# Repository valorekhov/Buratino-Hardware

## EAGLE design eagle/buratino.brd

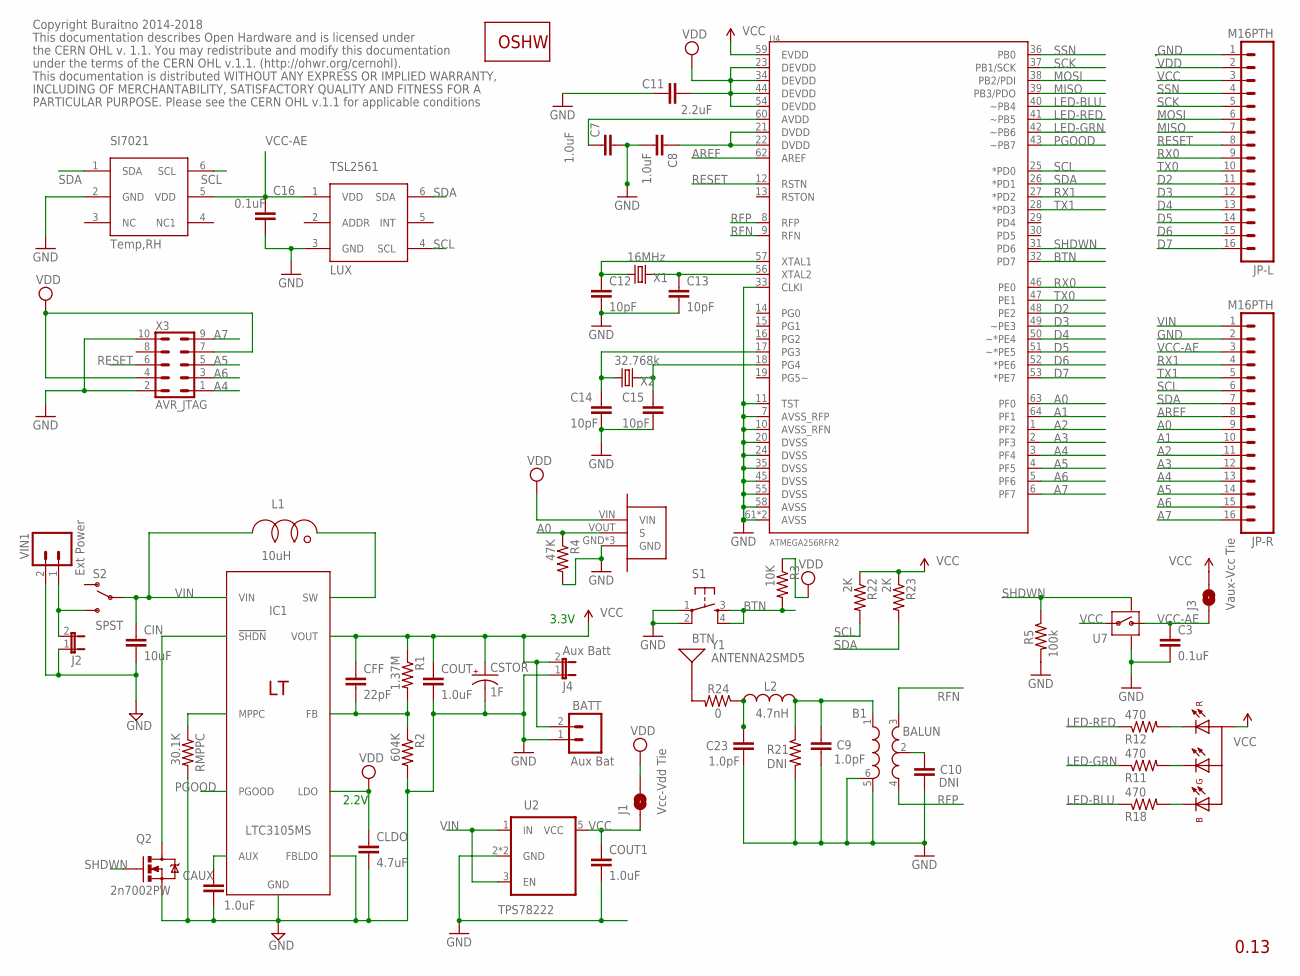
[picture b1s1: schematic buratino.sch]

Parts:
B1: BALUN
BATT: Aux Bat; JST-SFH
C3, C16: 0.1uF; 0603-CAP
C7, C8: 1.0uF; 0603-CAP
C9, C23: 1.0pF; 0402-CAP
C10: DNI; 0402-CAP
C11: 2.2uF; 0603-CAP
C12, C13, C14, C15: 10pF; 0402-CAP
CAUX: 1.0uF; 0603-CAP
CFF: 22pF; 0603-CAP
CIN: 10uF; 0805
CLDO: 4.7uF; 0603-CAP
COUT, COUT1: 1.0uF; 0603-CAP
CSTOR: 1F; SCAP1
IC1: LTC3105MS; MSOP12
J1: Vcc-Vdd Tie; SJ_2S-NO
J2: Ext Battery; 1X02
J3: Vaux-Vcc Tie; SJ_2S-NO
J4: Aux Batt; 1X02
JP-L: M16PTH; 1X16
JP-R: M16PTH; 1X16
L1: 10uH; NR2
L2: 4.7nH; 0402-CAP
PIR: IRS-B210ST01R1; PIRSMT
Q2: 2n7002PW; SOT323
R1: 1.37M; 0603-RES
R2: 604K; 0603-RES
R3: 10K; 0603-RES
R4: 47K; 0603-RES
R5: 100k; 0603-RES
R11, R12, R18: 470; 0603-RES
R21: DNI; 0402-RES
R22, R23: 2K; 0603-RES
R24: 0; 0402-RES
RMPPC: 30.1K; 0603-RES
S1: BTN; TACTILE-PTH
S2: SPST; SWITCH-SPDT-SMD
SI7021: Temp,RH; DFN6-3X3
TSL2561: LUX; DFN6-2X2
U2: TPS78222; SOT23-5
U4: ATMEGA256RFR2; QFN-64
U7: SWITCH; TDFN4
U8: LED-RGB; PLCC4
U$2: LOGO-OSHWSILKSCREEN; LOGO-OSHW-SS
VIN1: Ext Power; JST-SFH
X1: 16MHz; CRYSTAL-SMD-2.5X2-ABM10
X2: 32.768k; CRYSTAL-SMD-2X1.2-ABS06
X3: AVR_JTAG; PHB_1MM27_2X05_SNS
Y1: ANTENNA2SMD5; ANTENNA-CHIP5

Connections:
A0: JP-R.9, PIR.VOUT (S), R4.1, U4.63 (PF0)
A1: JP-R.10, U4.64 (PF1)
A2: JP-R.11, U4.1 (PF2)
A3: JP-R.12, U4.2 (PF3)
A4: JP-R.13, U4.3 (PF4), X3.1
A5: JP-R.14, U4.4 (PF5), X3.5
A6: JP-R.15, U4.5 (PF6), X3.3
A7: JP-R.16, U4.6 (PF7), X3.9
AREF: JP-R.8, U4.62 (AREF)
BTN: R3.2, S1.3, S1.4, U4.32 (PD7)
D2: JP-L.11, U4.48 (PE2)
D3: JP-L.12, U4.49 (~PE3)
D4: JP-L.13, U4.50 (~*PE4)
D5: JP-L.14, U4.51 (~*PE5)
D6: JP-L.15, U4.52 (*PE6)
D7: JP-L.16, U4.53 (*PE7)
GND: B1.5 (GND), B1.6 (GND), BATT.1, C3.2, C7.2, C8.2, C9.2, C10.2, C11.2, C12.2, C13.2, C14.2, C15.2, C16.2, C23.2, CAUX.2, CIN.2, CLDO.2, COUT.2, COUT1.2, CSTOR.2 (-), IC1.3 (FBLDO), IC1.6 (GND), IC1.7 (GND), J2.1, J4.1, JP-L.1, JP-R.2, PIR.GND, PIR.GND*1 (GND), PIR.GND*2 (GND), Q2.2 (S), R2.2, R4.2, R5.2, R21.2, RMPPC.2, S1.1, S1.2, SI7021.2 (GND), TSL2561.3 (GND), U2.2 (GND), U2.4 (GND), U4.7 (AVSS_RFP), U4.10 (AVSS_RFN), U4.11 (TST), U4.20 (DVSS), U4.24 (DVSS), U4.33 (CLKI), U4.35 (DVSS), U4.45 (DVSS), U4.55 (DVSS), U4.58 (AVSS), U4.61 (AVSS), U4.PADDLE (AVSS), U7.P$2 (GND), U7.P$5 (GND), VIN1.2, X1.P$2 (GND), X1.P$4 (GND), X3.2, X3.10
LED-BLU: R18.1, U4.40 (~PB4)
LED-GRN: R11.1, U4.42 (~PB6)
LED-RED: R12.1, U4.41 (~PB5)
MISO: JP-L.7, U4.39 (PB3/PDO)
MOSI: JP-L.6, U4.38 (PB2/PDI)
unnamed: R12.2, U8.P$1 (R-C)
unnamed: C23.1, L2.2, R24.1
unnamed: B1.1 (IN), C9.1, L2.1, R21.1
unnamed: R11.2, U8.P$4 (G-C)
unnamed: R18.2, U8.P$3 (B-C)
unnamed: C7.1, U4.60 (AVDD)
unnamed: IC1.9 (SW), L1.P$2 (B)
unnamed: B1.2 (RFGND), C10.1
unnamed: CAUX.1, IC1.12 (AUX)
unnamed: C12.1, U4.57 (XTAL1), X1.P$1 (1)
unnamed: C13.1, U4.56 (XTAL2), X1.P$3 (2)
unnamed: C14.1, U4.17 (PG3), X2.P$1 (1)
unnamed: C15.1, U4.18 (PG4), X2.P$2 (2)
unnamed: CFF.2, IC1.1 (FB), R1.2, R2.1
unnamed: C8.1, U4.21 (DVDD), U4.22 (DVDD)
unnamed: IC1.4 (!SHDN), Q2.3 (D)
unnamed: IC1.5 (MPPC), RMPPC.1
unnamed: J2.2, S2.3 (S), VIN1.1
unnamed: R24.2, Y1.FEED
PGOOD: IC1.10 (PGOOD), U4.43 (~PB7)
RESET: JP-L.8, U4.12 (RSTN), X3.6
RFN: B1.3 (OUT1), U4.9 (RFN)
RFP: B1.4 (OUT2), U4.8 (RFP)
RX0: JP-L.9, U4.46 (PE0)
RX1: JP-R.4, U4.27 (*PD2)
SCK: JP-L.5, U4.37 (PB1/SCK)
SCL: JP-R.6, R22.2, SI7021.6 (SCL), TSL2561.4 (SCL), U4.25 (*PD0)
SDA: JP-R.7, R23.2, SI7021.1 (SDA), TSL2561.6 (SDA), U4.26 (*PD1)
SHDWN: Q2.1 (G), R5.1, U4.31 (PD6), U7.P$4 (ON)
SSN: JP-L.4, U4.36 (PB0)
TX0: JP-L.10, U4.47 (PE1)
TX1: JP-R.5, U4.28 (*PD3)
VCC: BATT.2, CFF.1, COUT.1, COUT1.1, CSTOR.1 (+), IC1.11 (VOUT), J1.1, J3.2, J4.2, JP-L.3, R1.1, R22.1, R23.1, U2.5 (VCC), U4.59 (EVDD), U7.P$3 (IN), U8.P$2 (A)
VCC-AE: C3.1, C16.1, J3.1, JP-R.3, SI7021.5 (VDD), TSL2561.1 (VDD), U7.P$1 (OUT)
VDD: C11.1, CLDO.1, IC1.2 (LDO), J1.2, JP-L.2, PIR.VIN, R3.1, U4.23 (DEVDD), U4.34 (DEVDD), U4.44 (DEVDD), U4.54 (DEVDD), X3.4, X3.7
VIN: CIN.1, IC1.8 (VIN), JP-R.1, L1.P$1 (A), S2.2, U2.1 (IN), U2.3 (EN)

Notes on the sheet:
0.13
Copyright Buraitno 2014-2018
This documentation describes Open Hardware and is licensed under
the CERN OHL v. 1.1. You may redistribute and modify this documentation
under the terms of the CERN OHL v.1.1. (http://ohwr.org/cernohl).
This documentation is distributed WITHOUT ANY EXPRESS OR IMPLIED WARRANTY,
INCLUDING OF MERCHANTABILITY, SATISFACTORY QUALITY AND FITNESS FOR A
PARTICULAR PURPOSE. Please see the CERN OHL v.1.1 for applicable conditions
2.2V
3.3V

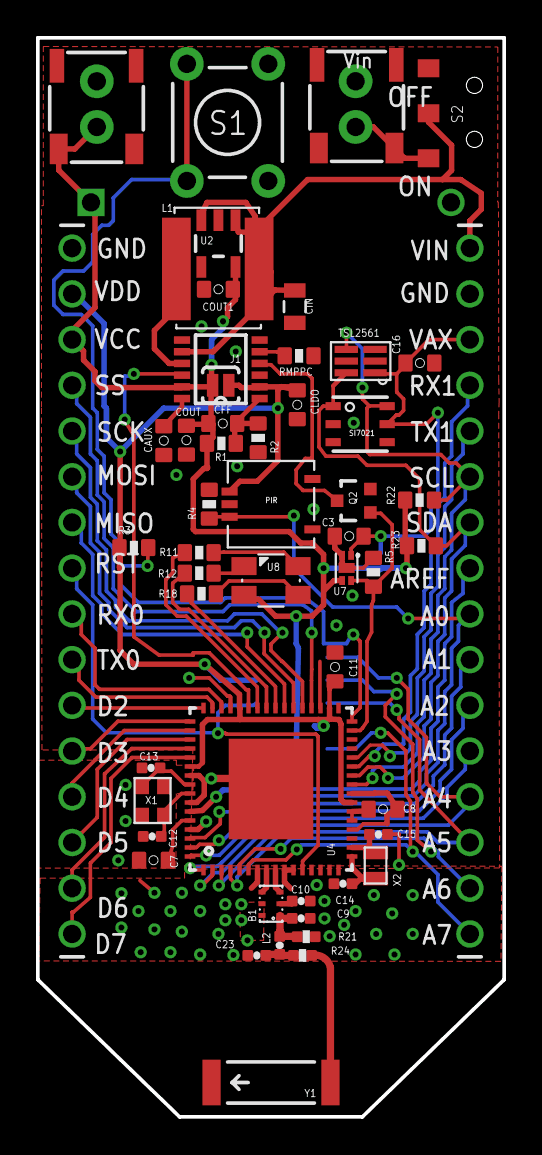
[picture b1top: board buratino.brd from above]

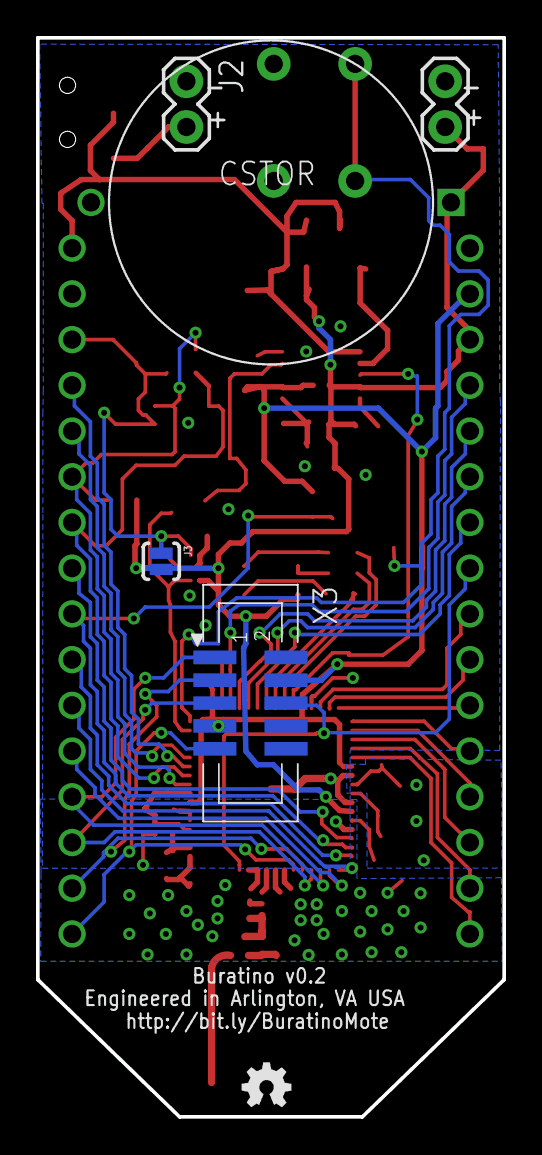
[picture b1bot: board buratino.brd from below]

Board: 2 copper layers, 25.9 x 59.9 mm, 59 parts (6 on the bottom side), 58 nets.

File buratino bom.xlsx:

PN | Value | Name | Device | Package | Parts | Qty
MCU
ATmega256RFR2-ZU | ATMEGA256RFR2 |  | ATMEGA128RFA1 | QFN-64 | U4 | 1
Tellurian 3960A 16MHz | 16MHz | Crystals | CRYSTALABM10 | CRYSTAL-SMD-2.5X2-ABM10 | X1 | 1
Tellurian 3960B 32.768k | 32.768k | Crystals | CRYSTAL-NOGND | CRYSTAL-SMD-2X1.2-ABS06 | X2 | 1
RF
2450BM15A0015E | BALUN | Atmega256RFR2 Balun | BALUN0805 | BALUN | B1 | 1
2450AT43A100E | ANTENNA2SMD5 | Atmega256RFR2 Antenna | ANTENNA2SMD5 | ANTENNA-CHIP5 | Y1 | 1
LQG15HS4N7S02D | 4.7nH | Inductor | INDUCTOR | 0402- | L2 | 1
Power - Battery, Ext Power
TPS78222 | 2.2v | Voltage Regulator LDO, 2.2v | LDO-TPS78233 | SOT23-5 | U2 | 1
AYZ0102AGRLC | SPST | SPST Switch | SWITCH-SPSTSMD2 | SWITCH-SPDT-SMD | S2 | 1
SIP32431DNP3-T1GE4TR-ND | SWITCH |  | SWITCH-MOSFETTDFN4 | TDFN4 | U7 | 1
LTC3105EMS#PBF | LTC3105MS | PV setup up converter | LTC3105MS | MSOP12 | IC1 | 1
2n7002PW |  | Pull down, enable control for LTC3105 | MOSFET-NCHANNEL2N7002PW | SOT323 | Q2 | 1
NR6045T100M | 10uH | Inductor for LTC3105 | NR6045T100M | NR2 | L1 | 1
EEC-RG0V105H | 1F | Optional super cap in the PV mode | EEC-RG0V105H | SCAP1 | CSTOR | 1
Sensors
SI7021-A10-GM1R |  | Temp & Humidity sensor (GM1R includes cover) | SI7021A10 | DFN6-3X3 | SI7021 | 1
TSL2561 |  | LUX sensor | TSL2561DFN | DFN6-2X2 | TSL2561 | 1
IRS-B210ST01R1 |  | PIR sensor | IRS-B210ST01R1 | PIRSMT | PIR | 1
Misc
C1005C0G1H010C | 1.0pF | Capacitor | CAP0402-CAP | 0402-CAP | C9, C23 | 2
C1005C0G1H100D050BA | 10pF | Loader Caps for Crystals | CAP0402-CAP | 0402-CAP | C12, C13, C14, C15 | 4
C1608NP01H220J080AA | 22pF | Capacitor | CAP0603-CAP | 0603-CAP | CFF | 1
C1608X8R1E104K080AA | 0.1uF | Capacitor | CAP0603-CAP | 0603-CAP | C3, C16 | 2
C1608X7R1A105M080AC | 1.0uF | Capacitor | CAP0603-CAP | 0603-CAP | CAUX, COUT, COUT1, C7, C8 | 5
C1608X7S1A225K080AC | 2.2uF | Capacitor | CAP0603-CAP | 0603-CAP | C11 | 1
C1608X7S1A475K080AC | 4.7uF | Capacitor | CAP0603-CAP | 0603-CAP | CLDO | 1
C2012X7R1A106K125AC | 10uF | Capacitor | CAP0805-CAP | 0805-CAP | CIN | 1
ERJ-2GE0R00X | 0 Ohm | 0 Ohm Resistor | RESISTOR0402-RES | 0402-RES | R24 | 1
ERJ-3GEYJ471V | 470 Ohm | Resistor | RESISTOR0603-RES | 0603-RES | R11, R12, R18 | 3
ERJ-3GEYJ202V | 2K | Resistor | RESISTOR0603-RES | 0603-RES | R22, R23 | 2
ERJ-3GEYJ103V | 10K | Resistor | RESISTOR0603-RES | 0603-RES | R3 | 1
ERJ-3EKF3012V | 30.1K | Resistor | RESISTOR0603-RES | 0603-RES | RMPPC | 1
ERJ-3GEYJ473V | 47K | Resistor | RESISTOR0603-RES | 0603-RES | R4 | 1
ERJ-3GEYJ104V | 100k | Resistor | RESISTOR0603-RES | 0603-RES | R5 | 1
ERJ-3EKF6043V | 604K | Resistor | RESISTOR0603-RES | 0603-RES | R2 | 1
ERJ-3EKF1374V | 1.37M | Resistor | RESISTOR0603-RES | 0603-RES | R1 | 1
 | BTN | Momentary Switch | TAC_SWITCHPTH | TACTILE-PTH | S1 | 1
CLVBA-FKA-CAEDH8BBB7A363 or CLV1A-FKB-CJ1M1F1BB7R4S3CT-ND | LED-RGB | LED-Bicolor Red/Green | LED-RGBPLCC4 | PLCC4 | U8 | 1
TS-132-G-A | M16PTH |  | M16PTH | 1X16 | JP-L, JP-R | 1
SM02B-SFHRS-TF(LF)(SN) | SMT power header |  | M02JST-SFH | JST-SFH | BATT, VIN1 | 2

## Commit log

2014-08-28 :boom::camel: Added .gitattributes & .gitignore files
2014-08-29 replace ICSP with JTAG
2014-08-30 replace 2mm headers with 0.1" headers
2014-09-01 add PIR
2014-09-01 pre-fab
2014-09-02 add BOM, final tweaks

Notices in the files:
eagle/buratino.brd:
Licensed under CERN OHL v.1.1
parts and their libraries:
SparkFun-DiscreteSemi: Licensing: Creative Commons ShareAlike 4.0 International - https://creativecommons.org/licenses/by-sa/4.0
